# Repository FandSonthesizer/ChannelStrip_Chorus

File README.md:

# ChannelStrip_Chorus
This is part of our modular mixer project
A channel strip module that implements a chorus functionality.

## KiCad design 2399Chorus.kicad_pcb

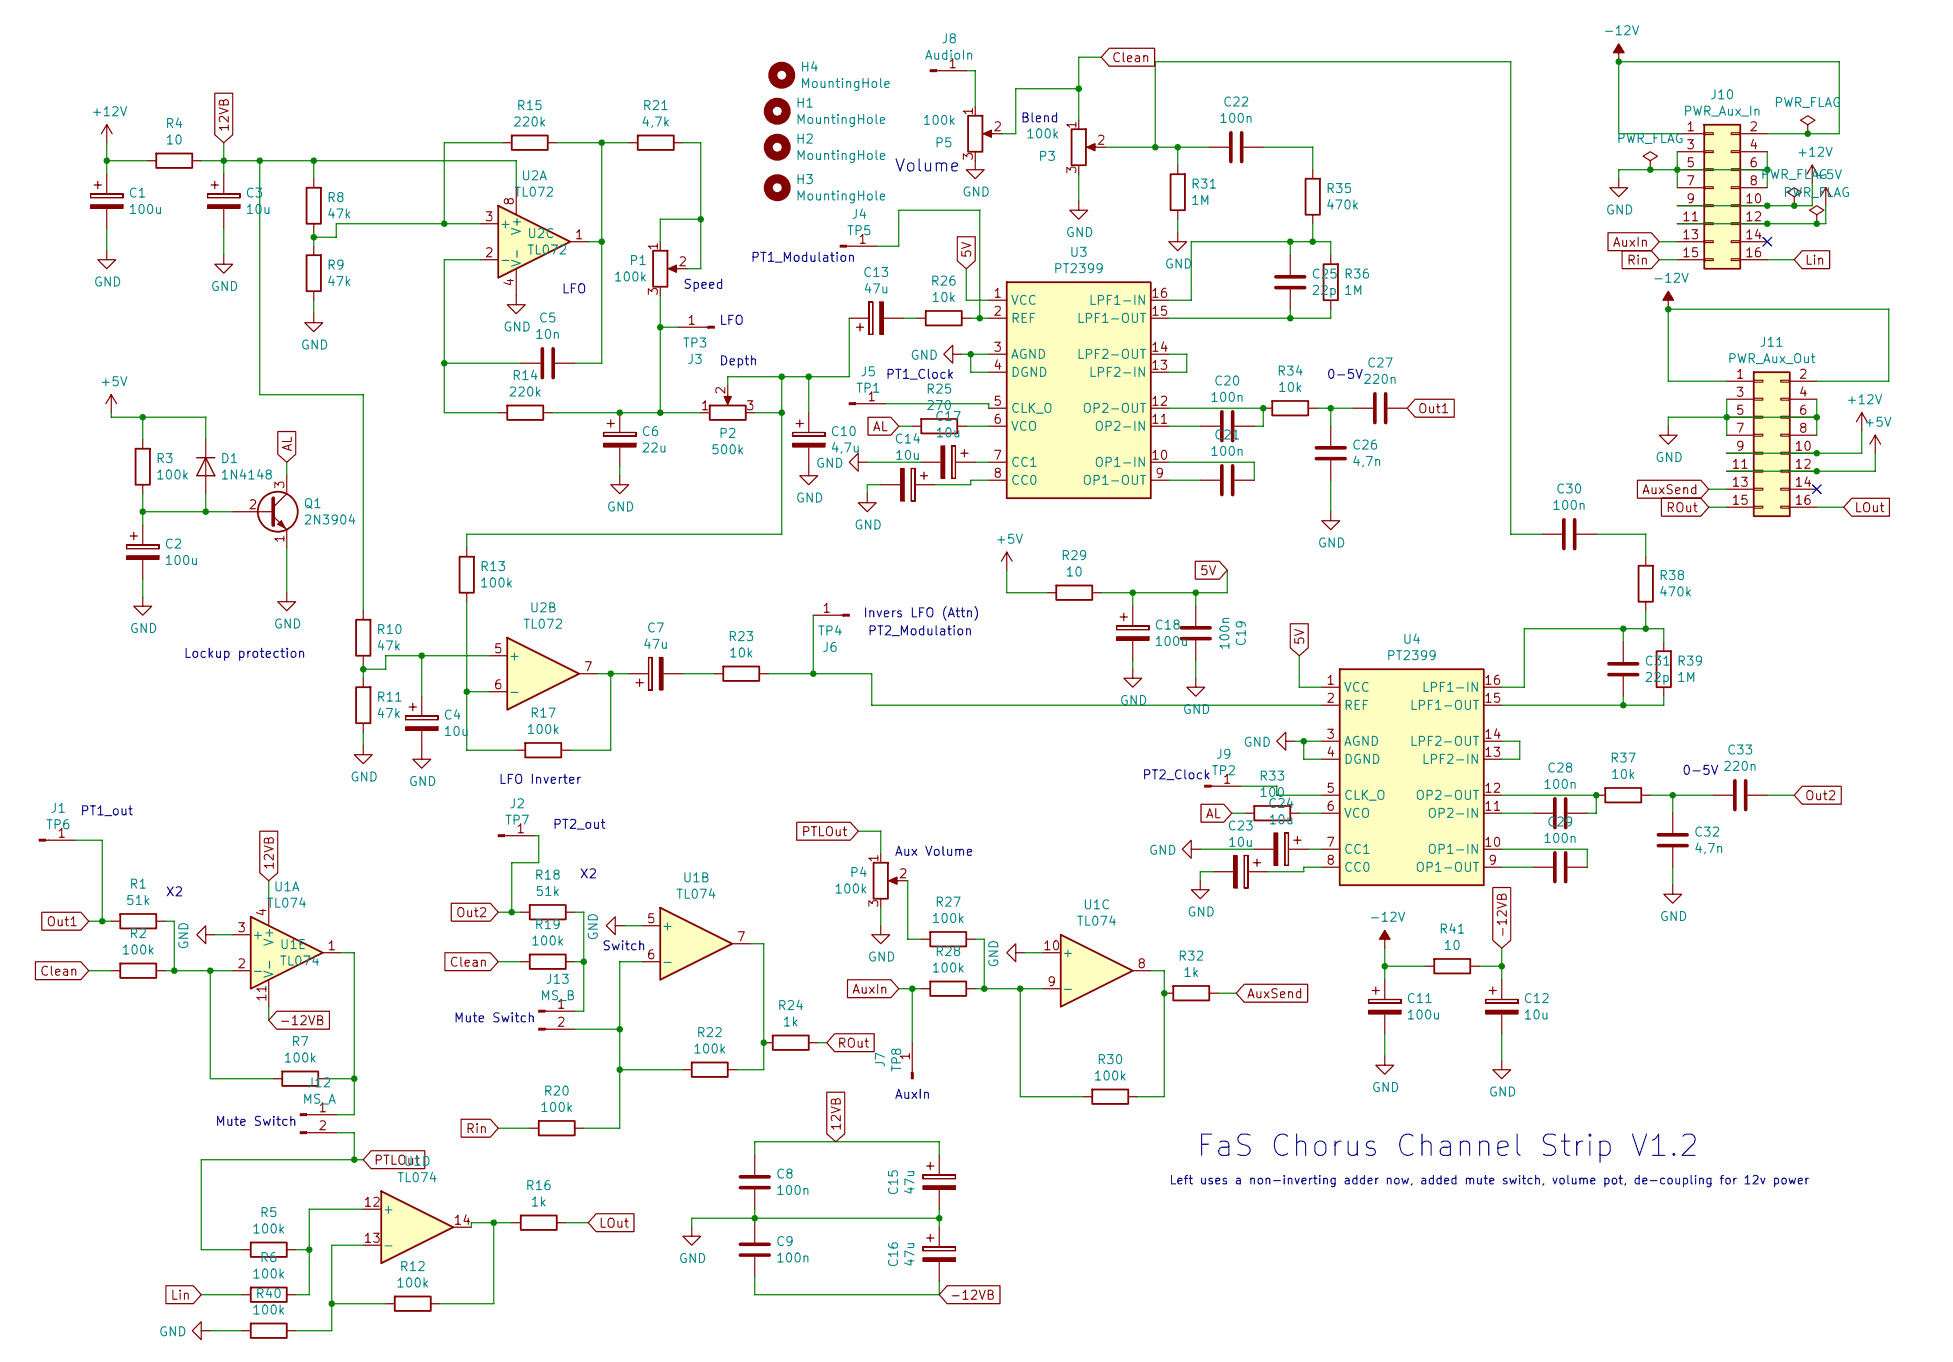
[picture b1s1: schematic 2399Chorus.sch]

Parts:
C1, C2, C11, C18: 100u; Elko_D6.3mm_P2.50mm
C3, C4, C12, C14, C17, C23, C24: 10u; Elko_D6.3mm_P2.50mm
C5: 10n; Kondensator_Keramik
C6: 22u; Elko_D6.3mm_P2.50mm
C7, C13, C15, C16: 47u; Elko_D6.3mm_P2.50mm
C8, C9, C19, C20, C21, C22, C28, C29, C30: 100n; Kondensator_Keramik
C10: 4,7u; Elko_D6.3mm_P2.50mm
C25, C31: 22p; Kondensator_Keramik
C26, C32: 4,7n; Kondensator_Keramik
C27, C33: 220n; Kondensator_Keramik
D1: 1N4148; Diode_Horizontal
H1, H2, H3, H4: MountingHole; MountHole
J1: TP6; Stift
J2: TP7; Stift
J3: TP3; Stift
J4: TP5; Stift
J5: TP1; Stift
J6: TP4; Stift
J7: TP8; Stift
J8: AudioIn; Stift
J9: TP2; Stift
J10: PWR_Aux_In; PinHeader_2x08_P2.54mm_Vertical
J11: PWR_Aux_Out; PinHeader_2x08_P2.54mm_Vertical
J12: MS_A; Stift_x02
J13: MS_B; Stift_x02
P1, P3, P4, P5: 100k; Trimmer_Vertical
P2: 500k; Trimmer_Vertical
Q1: 2N3904; TO-92L_Wide
R1, R18: 51k; Widerstand_liegend
R2, R3, R5, R6, R7, R12, R13, R17, R19, R20, R22, R27, R28, R30, R40: 100k; Widerstand_liegend
R4, R29, R41: 10; Widerstand_liegend
R8, R9, R10, R11: 47k; Widerstand_liegend
R14, R15: 220k; Widerstand_liegend
R16, R24, R32: 1k; Widerstand_liegend
R21: 4,7k; Widerstand_liegend
R23, R26, R34, R37: 10k; Widerstand_liegend
R25: 270; Widerstand_liegend
R31, R36, R39: 1M; Widerstand_liegend
R33: 100; Widerstand_liegend
R35, R38: 470k; Widerstand_liegend
U1: TL074; DIP-14_W7.62mm_Socket_LongPads
U2: TL072; DIP-8_W7.62mm_Socket_LongPads
U3, U4: PT2399; DIP-16_W7.62mm_Socket_LongPads

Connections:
5V: C18.1, C19.2, R29.1, U3.1 (VCC), U4.1 (VCC)
12VB: C3.1, C8.2, C15.1, R4.1, R8.2, R10.2, U1.4 (V+), U2.8 (V+)
+5V: D1.1 (K), J10.11, J10.12, J11.11, J11.12, R3.2, R29.2
+12V: C1.1, J10.9, J10.10, J11.9, J11.10, R4.2
-12V: C11.1, J10.1, J10.2, J11.1, J11.2, R41.2
-12VB: C9.1, C12.1, C16.2, R41.1, U1.11 (V-)
AL: Q1.3 (C), R25.2, R33.2
AuxIn: J7.1, J10.13, R28.2
AuxSend: J11.13, R32.1
Clean: P3.1, P5.2, R2.2, R19.2
GND: C1.2, C2.2, C3.2, C4.2, C6.2, C8.1, C9.2, C10.2, C11.2, C12.2, C14.2, C15.2, C16.1, C17.2, C18.2, C19.1, C23.2, C24.2, C26.1, C32.1, J10.3, J10.4, J10.5, J10.6, J10.7, J10.8, J11.3, J11.4, J11.5, J11.6, J11.7, J11.8, P3.3, P4.3, P5.3, Q1.1 (E), R9.1, R11.1, R31.1, R40.2, U1.3 (+), U1.5 (+), U1.10 (+), U2.4 (V-), U3.3 (AGND), U3.4 (DGND), U4.3 (AGND), U4.4 (DGND)
LOut: J11.16, R16.1
Lin: J10.16, R6.2
unnamed: C2.1, D1.2 (A), Q1.2 (B), R3.1
unnamed: C4.1, R10.1, R11.2, U2.5 (+)
unnamed: C5.1, R15.1, R21.2, U2.1
unnamed: C5.2, R14.2, U2.2 (-)
unnamed: C6.1, J3.1, P1.3, P2.1, R14.1
unnamed: C7.1, R17.1, U2.7
unnamed: C7.2, R23.2
unnamed: C10.1, C13.1, P2.2, P2.3, R13.2
unnamed: C13.2, R26.2
unnamed: C14.1, U3.8 (CC0)
unnamed: C17.1, U3.7 (CC1)
unnamed: C20.1, R34.2, U3.12 (OP2-OUT)
unnamed: C20.2, U3.11 (OP2-IN)
unnamed: C21.1, U3.10 (OP1-IN)
unnamed: C21.2, U3.9 (OP1-OUT)
unnamed: C22.1, R35.2
unnamed: C22.2, C30.2, P3.2, R31.2
unnamed: C23.1, U4.8 (CC0)
unnamed: C24.1, U4.7 (CC1)
unnamed: C25.1, R36.1, U3.15 (LPF1-OUT)
unnamed: C25.2, R35.1, R36.2, U3.16 (LPF1-IN)
unnamed: C26.2, C27.2, R34.1
unnamed: C28.1, R37.2, U4.12 (OP2-OUT)
unnamed: C28.2, U4.11 (OP2-IN)
unnamed: C29.1, U4.10 (OP1-IN)
unnamed: C29.2, U4.9 (OP1-OUT)
unnamed: C30.1, R38.2
unnamed: C31.1, R39.1, U4.15 (LPF1-OUT)
unnamed: C31.2, R38.1, R39.2, U4.16 (LPF1-IN)
unnamed: C32.2, C33.2, R37.1
unnamed: J4.1, R26.1, U3.2 (REF)
unnamed: J5.1, U3.5 (CLK_O)
unnamed: J6.1, R23.1, U4.2 (REF)
unnamed: J8.1, P5.1
unnamed: J9.1, U4.5 (CLK_O)
unnamed: J12.1, R7.1, U1.1
unnamed: J13.1, R18.1, R19.1
unnamed: J13.2, R20.1, R22.2, U1.6 (-)
unnamed: P1.1, P1.2, R21.1
unnamed: P4.2, R27.2
unnamed: R1.1, R2.1, R7.2, U1.2 (-)
unnamed: R5.1, R6.1, U1.12 (+)
unnamed: R12.1, R16.2, U1.14
unnamed: R12.2, R40.1, U1.13 (-)
unnamed: R13.1, R17.2, U2.6 (-)
unnamed: R8.1, R9.2, R15.2, U2.3 (+)
unnamed: R22.1, R24.2, U1.7
unnamed: R25.1, U3.6 (VCO)
unnamed: R27.1, R28.1, R30.2, U1.9 (-)
unnamed: R30.1, R32.2, U1.8
unnamed: R33.1, U4.6 (VCO)
unnamed: U3.13 (LPF2-IN), U3.14 (LPF2-OUT)
unnamed: U4.13 (LPF2-IN), U4.14 (LPF2-OUT)
Out1: C27.1, J1.1, R1.2
Out2: C33.1, J2.1, R18.2
PTLOut: J12.2, P4.1, R5.2
ROut: J11.15, R24.1
Rin: J10.15, R20.2

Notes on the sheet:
Depth
Speed
LFO Inverter
LFO
Lockup protection
Blend
0-5V
PT1_Clock
PT2_Clock
Invers LFO (Attn)
PT1_Modulation
PT2_Modulation
PT1_out
PT2_out
AuxIn
Switch
Mute Switch
Aux Volume
FaS Chorus Channel Strip V1.2
Volume
Left uses a non-inverting adder now, added mute switch, volume pot, de-coupling for 12v power

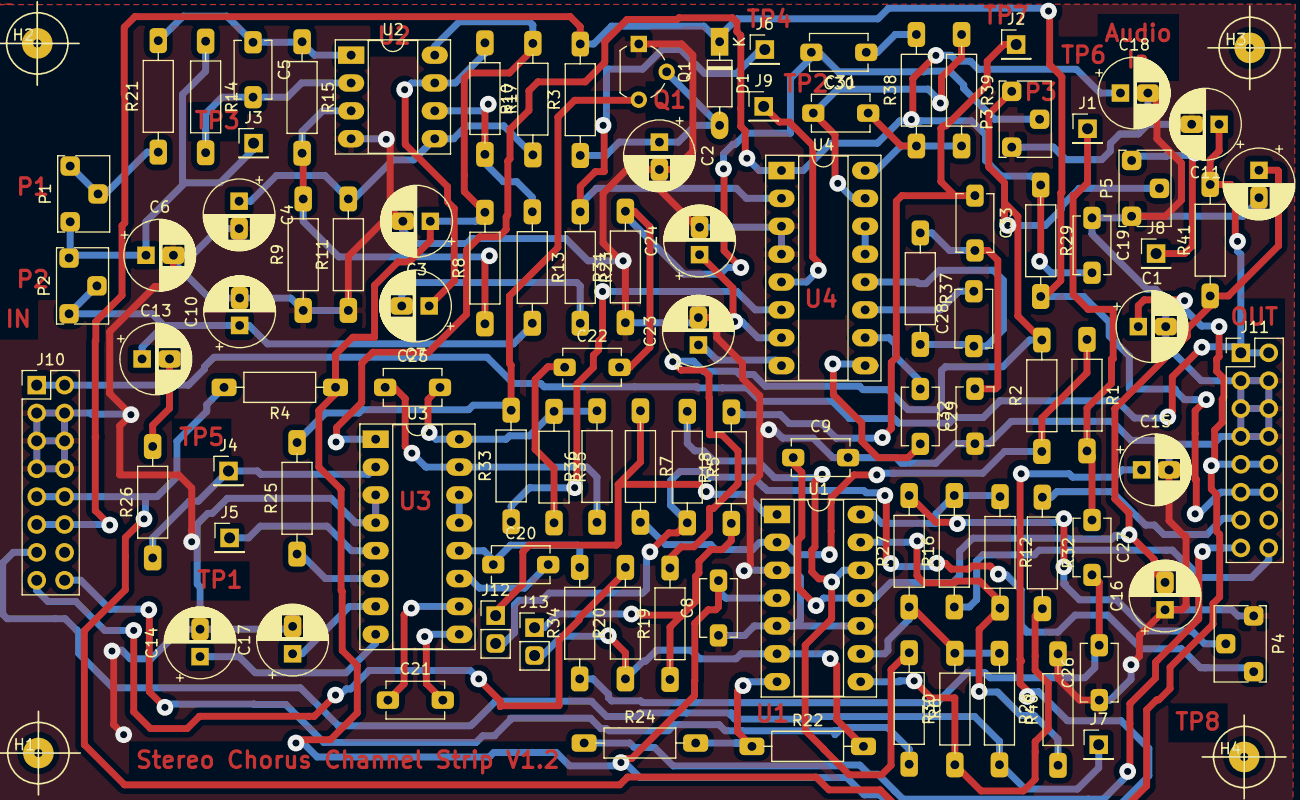
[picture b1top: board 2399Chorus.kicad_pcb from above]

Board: 2 copper layers, 102 parts (0 on the bottom side), 71 nets.

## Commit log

2020-05-07 Add files via upload
    Channel strip chorus using Pt2399
